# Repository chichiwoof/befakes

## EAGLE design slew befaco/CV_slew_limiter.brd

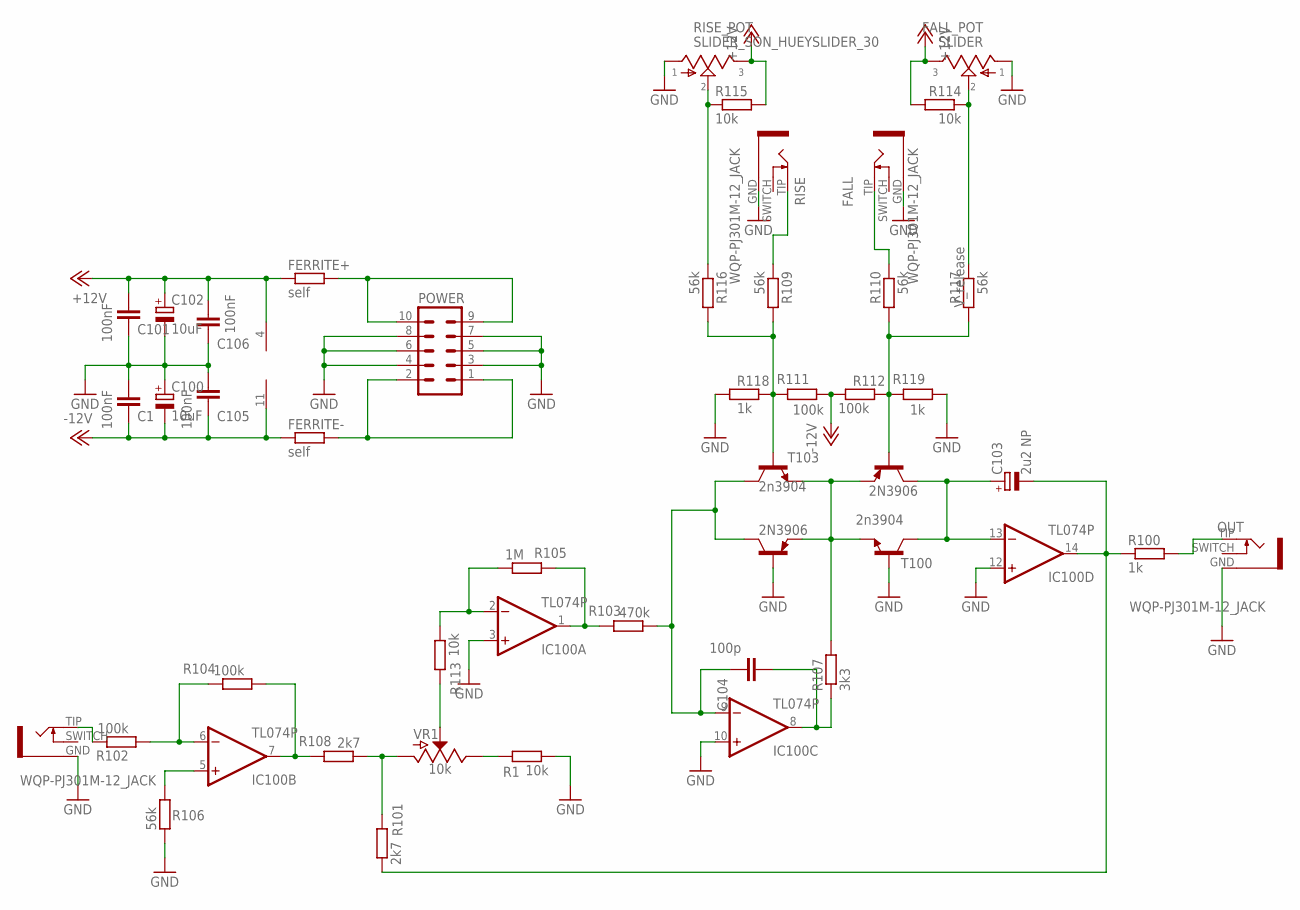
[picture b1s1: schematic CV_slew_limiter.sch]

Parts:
C1, C101, C105, C106: 100nF; C050-025X075
C100, C102: 10uF; E2-4
C103: 2u2 NP; E2-4
C104: 100p; C050-025X075
FALL: WQP-PJ301M-12_JACK
FALL_POT: SLIDER; SILDER_30
FERRITE+: self; 0204/5
FERRITE-: self; 0204/5
IC100: TL074P; DIL14
IN: WQP-PJ301M-12_JACK
OUT: WQP-PJ301M-12_JACK
POWER: ML10
R1, R113, R114, R115: 10k; 0204/5
R100, R118, R119: 1k; 0204/5
R101, R108: 2k7; 0204/5
R102, R104, R111, R112: 100k; 0204/5
R103: 470k; 0204/5
R105: 1M; 0204/5
R106, R109, R110, R116, R117: 56k; 0204/5
R107: 3k3; 0204/5
RISE: WQP-PJ301M-12_JACK
RISE_POT: SLIDER_SON_HUEYSLIDER_30; SILDER_30
T100, T103: 2n3904; TO92-EBC
T101, T102: 2N3906; TO92-EBC
VR1: 10k; POT-PTH-ALPS

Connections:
+12V: C101.2, C102.+, C106.2, FALL_POT.3, FERRITE+.1, IC100.4 (V+), R114.2, R115.2, RISE_POT.3
-12V: C1.1, C100.-, C105.1, FERRITE-.1, IC100.11 (V-), R111.1, R112.1
GND: C1.2, C100.+, C101.1, C102.-, C105.2, C106.1, FALL.GND (1), FALL_POT.1, IC100.3 (+IN), IC100.10 (+IN), IC100.12 (+IN), IN.GND (1), OUT.GND (1), POWER.3, POWER.4, POWER.5, POWER.6, POWER.7, POWER.8, R1.1, R106.2, R118.1, R119.1, RISE.GND (1), RISE_POT.1, T100.B, T102.B
IC25: C103.-, IC100.14 (OUT), R100.1, R101.1
unnamed: OUT.TIP (2), R100.2
unnamed: R113.2, VR1.P$2 (S)
unnamed: R101.2, R108.1, VR1.P$3 (A)
unnamed: IN.TIP (2), R102.2
unnamed: R1.2, VR1.P$1 (E)
unnamed: FERRITE+.2, POWER.9, POWER.10
unnamed: R107.2, T100.E, T101.E, T102.E, T103.E
unnamed: C103.+, IC100.13 (-IN), T100.C, T101.C
unnamed: IC100.2 (-IN), R105.1, R113.1
unnamed: C104.1, IC100.9 (-IN), R103.1, T102.C, T103.C
unnamed: C104.2, IC100.8 (OUT), R107.1
unnamed: R109.1, RISE.TIP (2)
unnamed: IC100.1 (OUT), R103.2, R105.2
unnamed: IC100.7 (OUT), R104.1, R108.2
unnamed: FERRITE-.2, POWER.1, POWER.2
unnamed: IC100.6 (-IN), R102.1, R104.2
unnamed: IC100.5 (+IN), R106.1
unnamed: R115.1, R116.1, RISE_POT.2
unnamed: FALL_POT.2, R114.1, R117.1
unnamed: FALL.TIP (2), R110.1
TO_ATTACK_CV: R109.2, R111.2, R116.2, R118.2, T103.B
TO_DECCAY_CV: R110.2, R112.2, R117.2, R119.2, T101.B

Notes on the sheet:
V_release

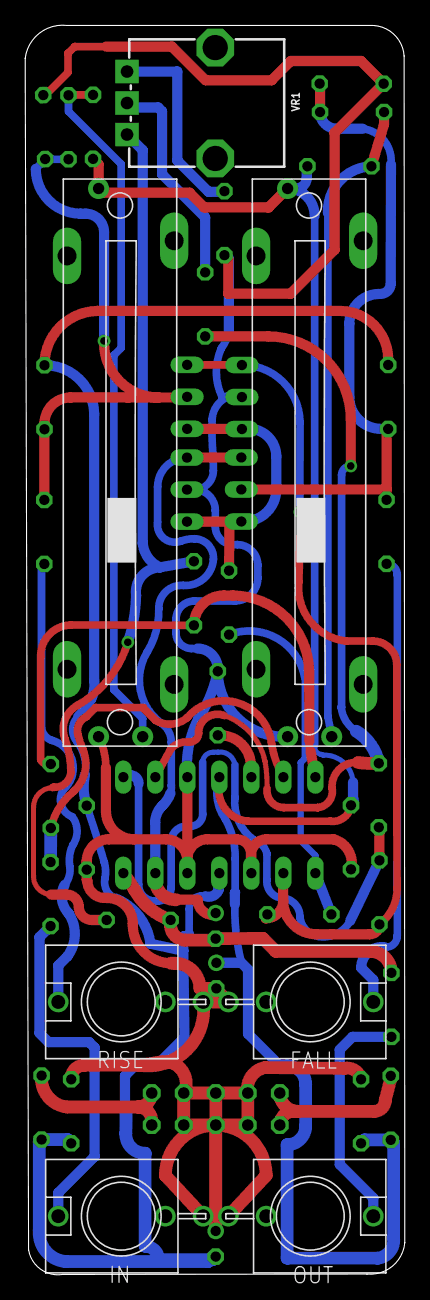
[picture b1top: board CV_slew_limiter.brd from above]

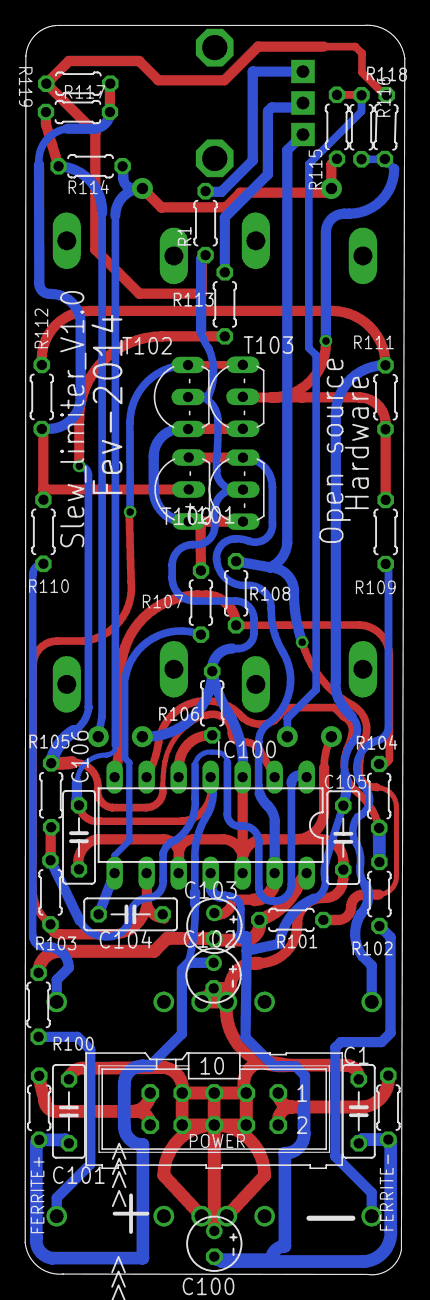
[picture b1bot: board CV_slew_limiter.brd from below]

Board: 2 copper layers, 30.1 x 99.2 mm, 44 parts (37 on the bottom side), 26 nets.

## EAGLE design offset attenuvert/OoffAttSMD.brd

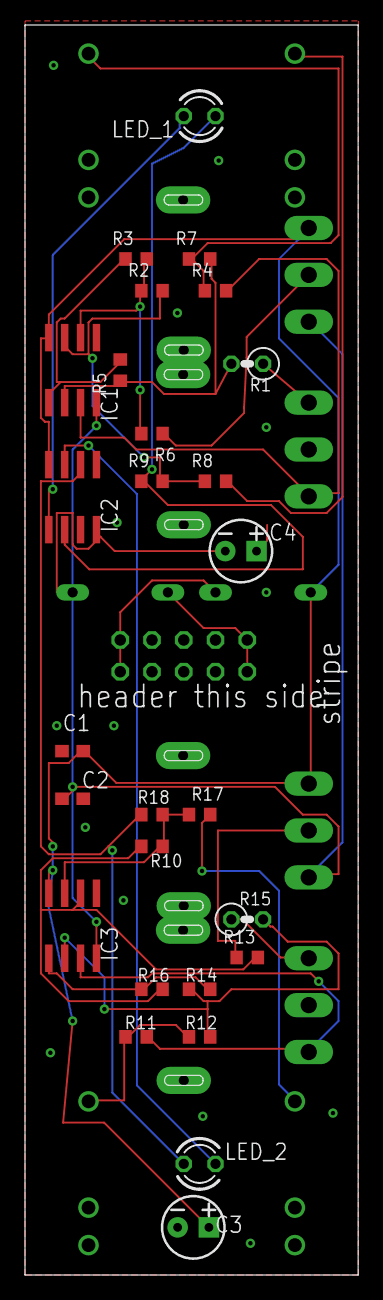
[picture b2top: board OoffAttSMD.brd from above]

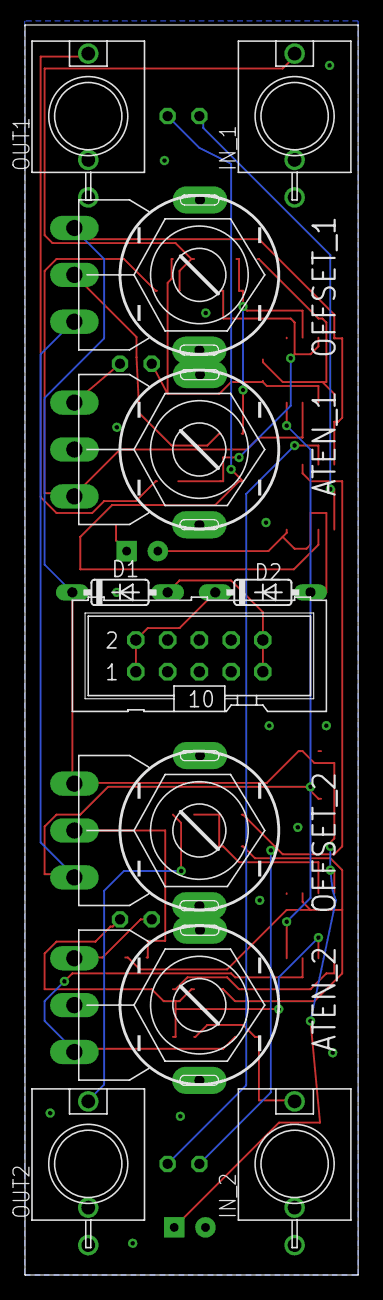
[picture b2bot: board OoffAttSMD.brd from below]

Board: 2 copper layers, 26.6 x 100.0 mm, 38 parts (11 on the bottom side), 27 nets.

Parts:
ATEN_1, ATEN_2: R1212NPADS_GRANDES; R121N
C1, C2: 100n; C0603
C3, C4: 10uF; CPOL-RADIAL-2.5MM-5MM
D1, D2: DO35-7
IC1, IC2, IC3: TL072D; SO08
IN_1, IN_2: WQP-PJ301M-12_JACK
LED_1, LED_2: LED3MM
OFFSET_1, OFFSET_2: R1212NPADS_GRANDES; R121N
OUT1, OUT2: WQP-PJ301M-12_JACK
POWER: ML10
R1, R15: 43k; 0207/2V
R2, R3, R6, R10, R13, R16: 10k; R0603
R4, R5, R7, R11, R12, R14: 100k; R0603
R8, R17: 1k; R0603
R9, R18: 3k; R0603

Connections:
+12V: C1.2, C3.1, D1.C, IC1.8, IC2.8, IC3.8, OFFSET_1.PIN1, OFFSET_2.PIN1
-12V: C2.1, C4.2, D2.A, IC1.4, IC2.4, IC3.4, OFFSET_1.PIN3, OFFSET_2.PIN3
GND: ATEN_1.C1, ATEN_1.C2, ATEN_1.PIN2, ATEN_2.C1, ATEN_2.C2, ATEN_2.PIN2, C1.1, C2.2, C3.2, C4.1, IC1.5, IC2.3, IC2.5, IC3.5, IN_1.P$3, IN_2.P$3, OFFSET_1.C1, OFFSET_1.C2, OFFSET_2.C1, OFFSET_2.C2, OUT1.P$3, OUT2.P$3, POWER.3, POWER.4, POWER.5, POWER.6, POWER.7, POWER.8
unnamed: D1.A, POWER.9, POWER.10
unnamed: D2.C, POWER.1, POWER.2
unnamed: IC2.1, LED_1.K
unnamed: IC3.2, R12.2, R14.1, R15.2
unnamed: ATEN_2.PIN3, IC3.3, R11.2
unnamed: IC3.1, R14.2, R16.1
unnamed: IN_2.P$1, R11.1, R12.1
unnamed: IC3.6, R10.1, R13.2, R16.2
unnamed: IC3.7, R10.2, R17.1, R18.2
unnamed: OFFSET_2.PIN2, R13.1
unnamed: ATEN_2.PIN1, R15.1
unnamed: OUT2.P$1, R17.2
unnamed: IC1.2, R1.2, R5.1, R7.2
unnamed: OUT1.P$1, R8.2
unnamed: ATEN_1.PIN3, IC1.3, R4.2
unnamed: IC2.7, LED_2.K
unnamed: IC2.6, LED_2.A, R18.1
unnamed: IC2.2, LED_1.A, R9.1
unnamed: ATEN_1.PIN1, R1.1
unnamed: IC1.1, R3.1, R5.2
unnamed: IN_1.P$1, R4.1, R7.1
unnamed: IC1.6, R2.1, R3.2, R6.2
unnamed: IC1.7, R2.2, R8.1, R9.2
unnamed: OFFSET_1.PIN2, R6.1

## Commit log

2020-05-25 init befaco clones

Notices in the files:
parts and their libraries:
SparkFun-Capacitors: Licensing: Creative Commons ShareAlike 4.0 International - https://creativecommons.org/licenses/by-sa/4.0
